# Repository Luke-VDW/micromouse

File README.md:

# micromouse
This repository contains all documentation used and deliverables produced for the UCT EEE3088F micromouse project.

A micromouse is a battery powered robot whose goal is to navigate through a maze. The project focuses on the design of the micro-mouse’s hardware. The project is compartmentalised into four subsystems, namely: the motherboard, the processor, power and sensing. The processor subsystem and motherboard subsystem have been completed. This repository will contain the power subsystem and sensing subsystem documentation.

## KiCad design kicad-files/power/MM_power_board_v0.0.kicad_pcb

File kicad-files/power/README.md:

This folder contains all kicad material for the power subsystem of the micromouse project.

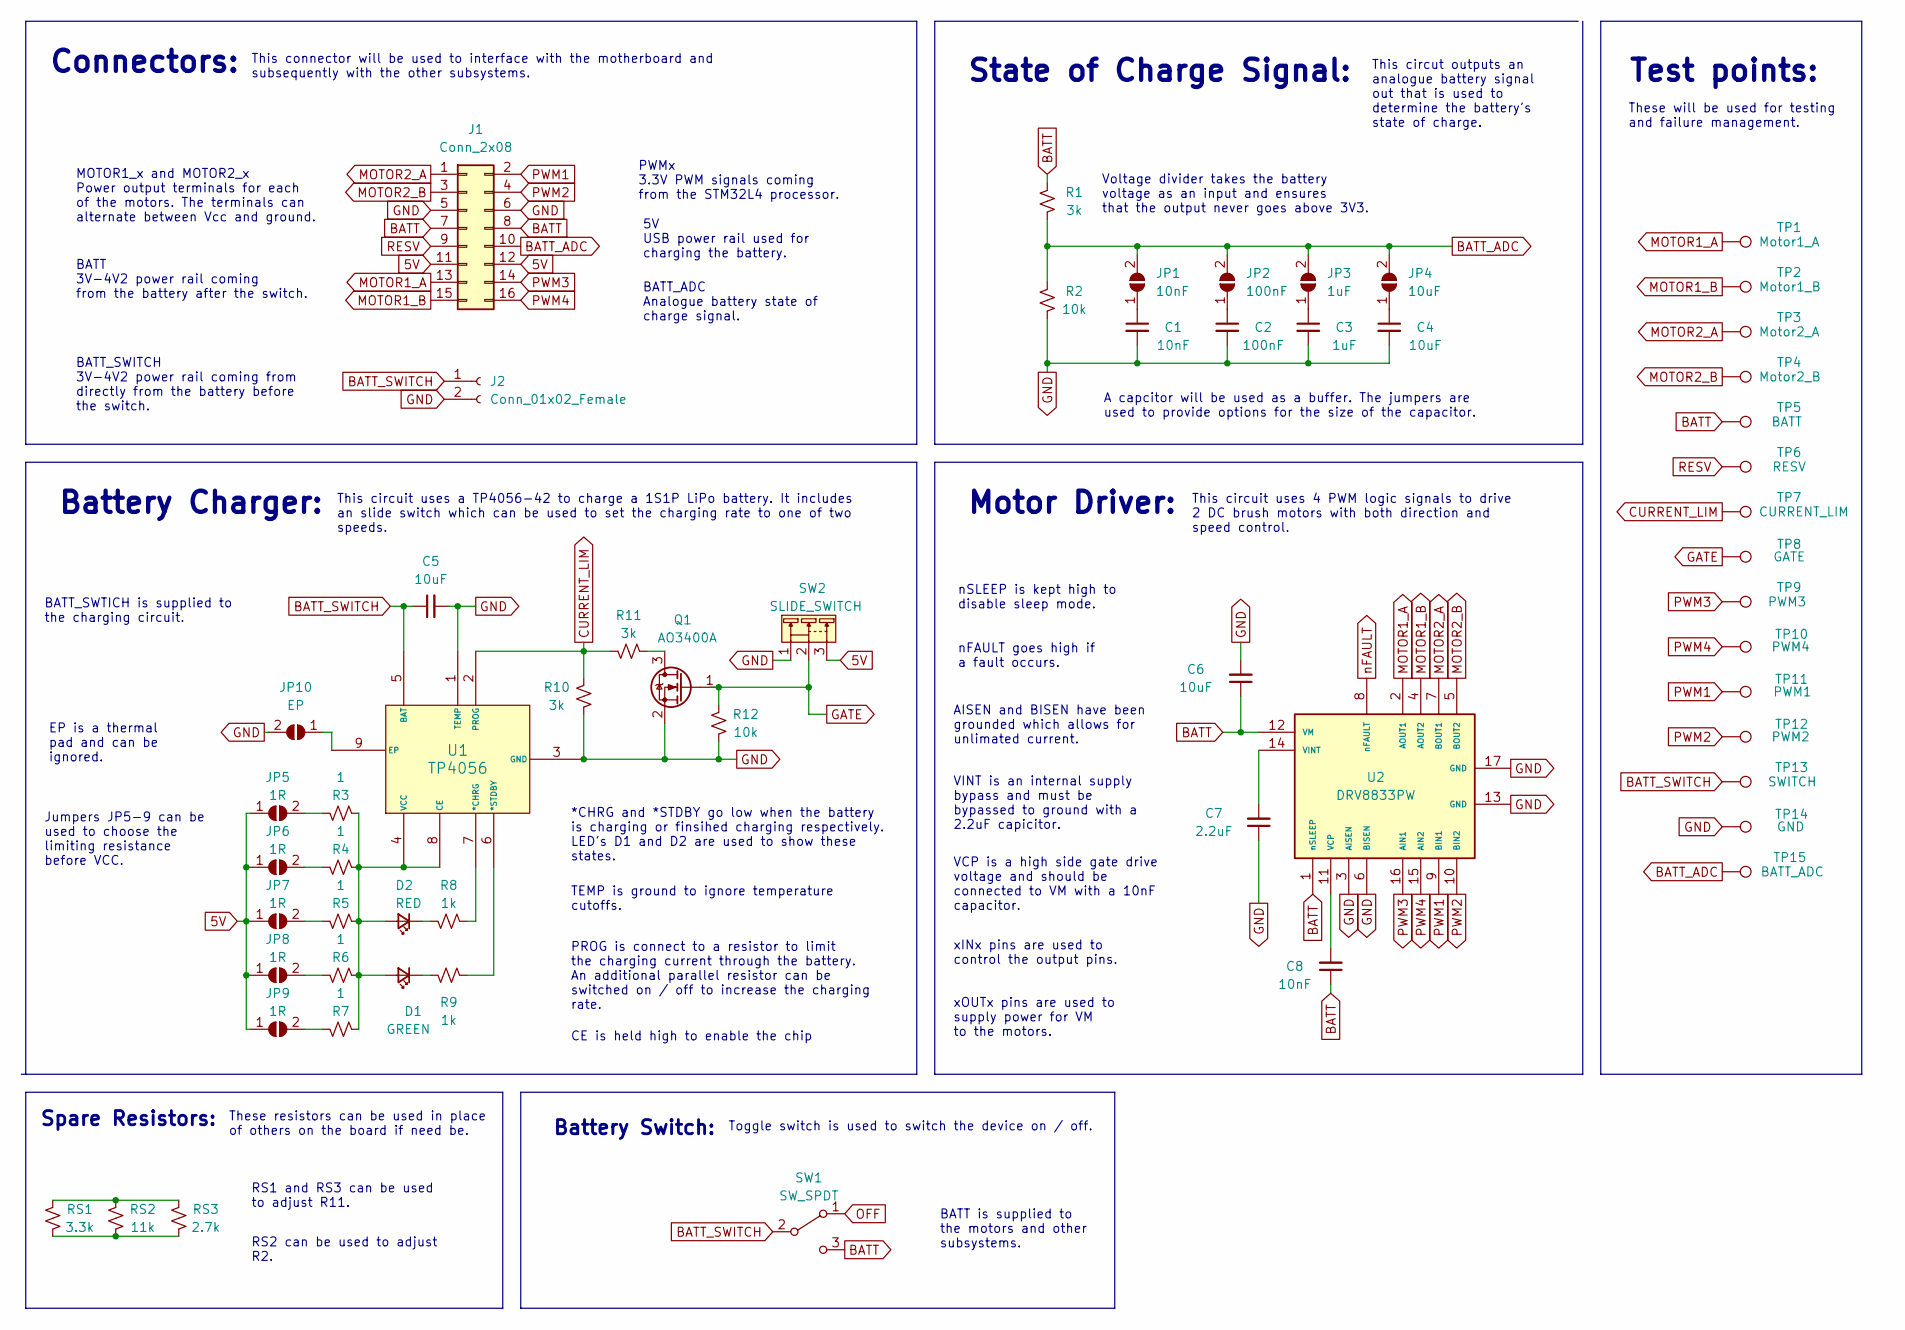
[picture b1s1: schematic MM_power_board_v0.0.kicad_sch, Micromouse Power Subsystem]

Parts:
C1, C8: 10nF; C_0603_1608Metric
C2: 100nF; C_0603_1608Metric
C3: 1uF; C_0603_1608Metric
C4, C5, C6: 10uF; C_0603_1608Metric
C7: 2.2uF; C_0603_1608Metric
D1: GREEN; LED0805-R-RD
D2: RED; LED0603-RD
J1: Conn_2x08; PinHeader_2x08_P2.54mm_Vertical
J2: Conn_01x02_Female; JST_PH_S2B-PH-K_1x02_P2.00mm_Horizontal
JP1: 10nF; SolderJumper-2_P1.3mm_Open_RoundedPad1.0x1.5mm
JP2: 100nF; SolderJumper-2_P1.3mm_Open_RoundedPad1.0x1.5mm
JP3: 1uF; SolderJumper-2_P1.3mm_Open_RoundedPad1.0x1.5mm
JP4: 10uF; SolderJumper-2_P1.3mm_Open_RoundedPad1.0x1.5mm
JP5, JP6, JP7, JP8, JP9: 1R; SolderJumper-2_P1.3mm_Open_RoundedPad1.0x1.5mm
JP10: EP; SolderJumper-2_P1.3mm_Open_RoundedPad1.0x1.5mm
Q1: AO3400A; SOT-23
R1, R10, R11: 3k; R_0603_1608Metric
R2, R12: 10k; R_0603_1608Metric
R3, R4, R5, R6, R7: 1; R_1206_3216Metric
R8, R9: 1k; R_0603_1608Metric
RS1: 3.3k; R_0603_1608Metric
RS2: 11k; R_0603_1608Metric
RS3: 2.7k; R_0603_1608Metric
SW1: SW_SPDT; SW-TH_MT-0-103-A101-M200-RS
SW2: SLIDE_SWITCH; SW-TH_SS-12D10L5
TP1: Motor1_A; TestPoint_Keystone_5000-5004_Miniature
TP2: Motor1_B; TestPoint_Keystone_5000-5004_Miniature
TP3: Motor2_A; TestPoint_Keystone_5000-5004_Miniature
TP4: Motor2_B; TestPoint_Keystone_5000-5004_Miniature
TP5: BATT; TestPoint_Keystone_5000-5004_Miniature
TP6: RESV; TestPoint_Keystone_5000-5004_Miniature
TP7: CURRENT_LIM; TestPoint_Keystone_5000-5004_Miniature
TP8: GATE; TestPoint_Keystone_5000-5004_Miniature
TP9: PWM3; TestPoint_Keystone_5000-5004_Miniature
TP10: PWM4; TestPoint_Keystone_5000-5004_Miniature
TP11: PWM1; TestPoint_Keystone_5000-5004_Miniature
TP12: PWM2; TestPoint_Keystone_5000-5004_Miniature
TP13: SWITCH; TestPoint_Keystone_5000-5004_Miniature
TP14: GND; TestPoint_Keystone_5000-5004_Miniature
TP15: BATT_ADC; TestPoint_Keystone_5000-5004_Miniature
U1: TP4056; ESOP-8_L4.9-W3.9-P1.27-LS6.0-BL-EP
U2: DRV8833PW; TSSOP-16_L5.0-W4.4-P0.65-LS6.4-BL-EP

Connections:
5V: J1.11, J1.12, JP5.1 (A), JP6.1 (A), JP7.1 (A), JP8.1 (A), JP9.1 (A), SW2.3
BATT: C6.1, C8.1, J1.7, J1.8, R1.2, SW1.3 (C), TP5.1, U2.1 (nSLEEP), U2.12 (VM)
BATT_ADC: J1.10, JP1.2 (B), JP2.2 (B), JP3.2 (B), JP4.2 (B), R1.1, R2.2, TP15.1
BATT_SWITCH: C5.1, J2.1, SW1.2 (B), TP13.1, U1.5 (BAT)
CURRENT_LIM: R10.2, R11.1, TP7.1, U1.2 (PROG)
GATE: Q1.1 (G), R12.1, SW2.2, TP8.1
GND: C1.2, C2.2, C3.2, C4.2, C5.2, C6.2, C7.1, J1.5, J1.6, J2.2, JP10.2 (B), Q1.2 (S), R2.1, R10.1, R12.2, SW2.1, TP14.1, U1.1 (TEMP), U1.3 (GND), U2.3 (AISEN), U2.6 (BISEN), U2.13 (GND), U2.17 (GND)
Motor1_A: J1.13, TP1.1, U2.2 (AOUT1)
Motor1_B: J1.15, TP2.1, U2.4 (AOUT2)
Motor2_A: J1.1, TP3.1, U2.7 (BOUT1)
Motor2_B: J1.3, TP4.1, U2.5 (BOUT2)
unnamed: C1.1, JP1.1 (A)
unnamed: C2.1, JP2.1 (A)
unnamed: C3.1, JP3.1 (A)
unnamed: C4.1, JP4.1 (A)
unnamed: C7.2, U2.14 (VINT)
unnamed: C8.2, U2.11 (VCP)
unnamed: D1.1 (K), R9.2
unnamed: D1.2 (A), D2.2 (A), R3.2, R4.2, R5.2, R6.2, R7.2, U1.4 (VCC), U1.8 (CE)
unnamed: D2.1 (K), R8.2
unnamed: JP5.2 (B), R3.1
unnamed: JP6.2 (B), R4.1
unnamed: JP7.2 (B), R5.1
unnamed: JP8.2 (B), R6.1
unnamed: JP9.2 (B), R7.1
unnamed: JP10.1 (A), U1.9 (EP)
unnamed: Q1.3 (D), R11.2
unnamed: R8.1, U1.7 (*CHRG)
unnamed: R9.1, U1.6 (*STDBY)
unnamed: RS1.1, RS2.1, RS3.1
unnamed: RS1.2, RS2.2, RS3.2
OFF: SW1.1 (A)
PWM1: J1.2, TP11.1, U2.9 (BIN1)
PWM2: J1.4, TP12.1, U2.10 (BIN2)
PWM3: J1.14, TP9.1, U2.16 (AIN1)
PWM4: J1.16, TP10.1, U2.15 (AIN2)
RESV: J1.9, TP6.1
nFAULT: U2.8 (nFAULT)

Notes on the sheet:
BATT is supplied to the motors and other subsystems.
EP is a thermal pad and can be ignored.
Battery Charger:
Jumpers JP5-9 can be used to choose the limiting resistance before VCC.
Voltage divider takes the battery voltage as an input and ensures that the output never goes above 3V3.
A capcitor will be used as a buffer. The jumpers are used to provide options for the size of the capacitor.
VINT is an internal supply bypass and must be bypassed to ground with a 2.2uF capicitor.
This circuit uses 4 PWM logic signals to drive 2 DC brush motors with both direction and speed control.
These resistors can be used in place of others on the board if need be.
BATT_ADC Analogue battery state of charge signal.
nFAULT goes high if a fault occurs.
State of Charge Signal:
These will be used for testing and failure management.
BATT 3V-4V2 power rail coming from the battery after the switch.
This circut outputs an analogue battery signal out that is used to determine the battery's state of charge.
RS2 can be used to adjust R2.
PROG is connect to a resistor to limit the charging current through the battery. An additional parallel resistor can be switched on / off to increase the charging rate.
BATT_SWITCH 3V-4V2 power rail coming from directly from the battery before the switch.
CE is held high to enable the chip
VCP is a high side gate drive voltage and should be connected to VM with a 10nF capacitor.
Connectors:
Battery Switch:
This connector will be used to interface with the motherboard and subsequently with the other subsystems.
xINx pins are used to control the output pins.
PWMx 3.3V PWM signals coming from the STM32L4 processor.
xOUTx pins are used to supply power for VM to the motors.
Spare Resistors:
TEMP is ground to ignore temperature cutoffs.
AISEN and BISEN have been grounded which allows for unlimated current.
RS1 and RS3 can be used to adjust R11.
5V USB power rail used for charging the battery.
Test points:
nSLEEP is kept high to disable sleep mode.
BATT_SWTICH is supplied to the charging circuit.
MOTOR1_x and MOTOR2_x Power output terminals for each of the motors. The terminals can alternate between Vcc and ground.
Toggle switch is used to switch the device on / off.
Motor Driver:
*CHRG and *STDBY go low when the battery is charging or finsihed charging respectively. LED's D1 and D2 are used to show these states.
This circuit uses a TP4056-42 to charge a 1S1P LiPo battery. It includes an slide switch which can be used to set the charging rate to one of two speeds.

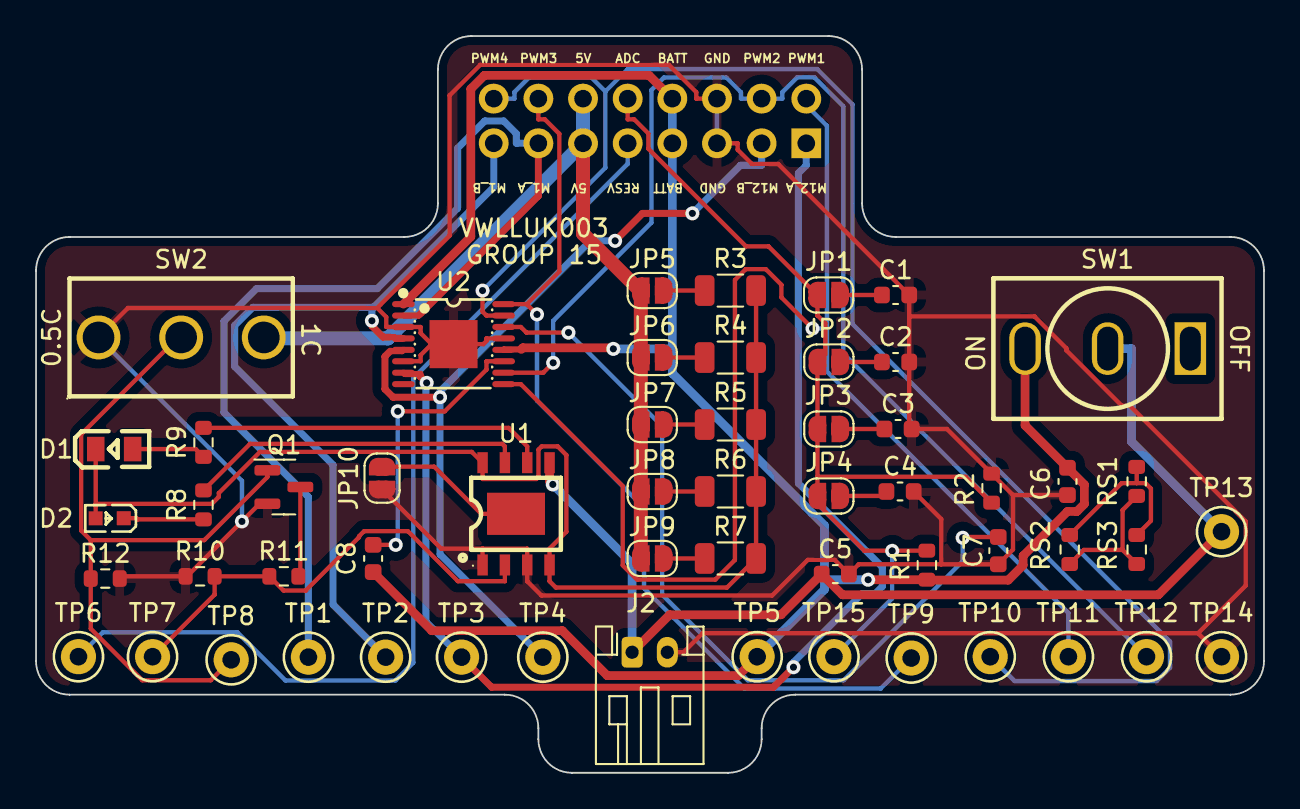
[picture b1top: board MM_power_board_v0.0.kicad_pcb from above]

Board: 2 copper layers, 69.9 x 41.9 mm, 57 parts (1 on the bottom side), 36 nets.

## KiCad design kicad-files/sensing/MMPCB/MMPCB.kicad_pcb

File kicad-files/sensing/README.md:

This folder contains all kicad material for the sensing subsystem of the micromouse project.

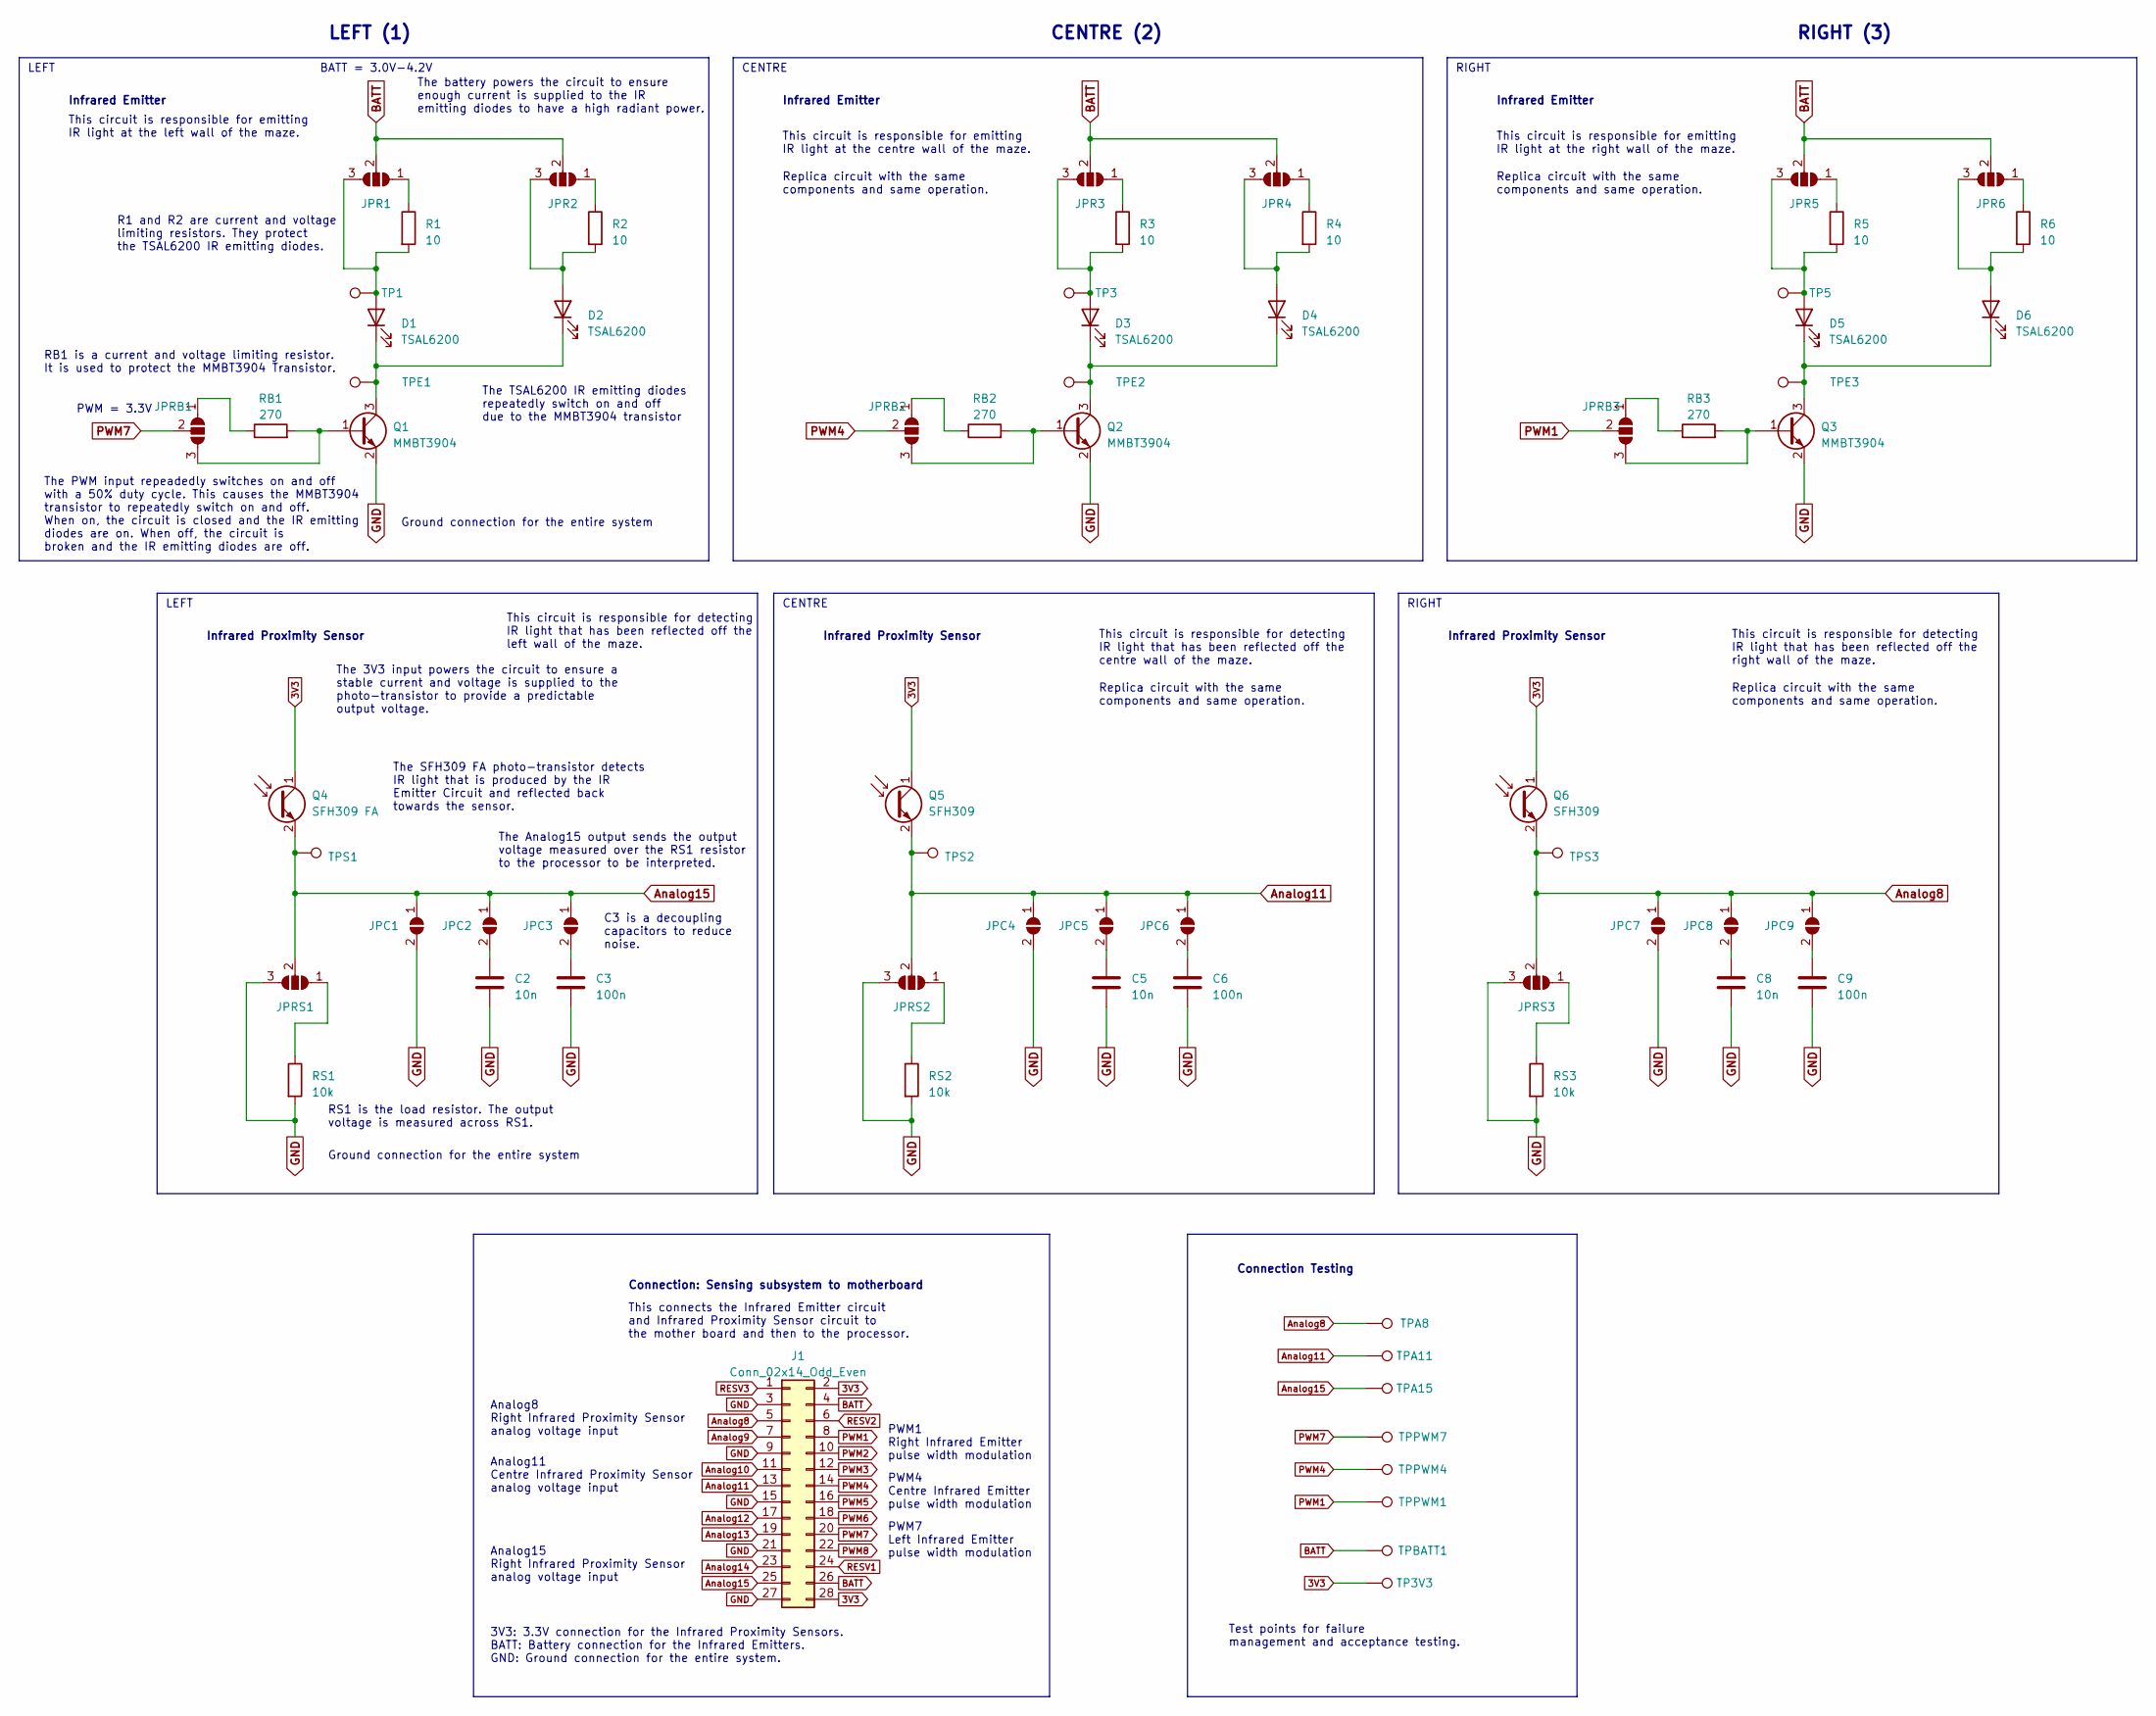
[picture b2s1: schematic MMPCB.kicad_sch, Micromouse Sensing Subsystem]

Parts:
C2, C5, C8: 10n; C_0603_1608Metric
C3, C6, C9: 100n; C_0603_1608Metric
D1, D2, D3, D4, D5, D6: TSAL6200; LED_D5.0mm_Horizontal_O1.27mm_Z3.0mm_Clear
J1: Conn_02x14_Odd_Even; PinHeader_2x14_P2.54mm_Vertical
JPC1, JPC2, JPC3, JPC4, JPC5, JPC6, JPC7, JPC8, JPC9: SolderJumper-2_P1.3mm_Open_RoundedPad1.0x1.5mm
JPR1, JPR2, JPR3, JPR4, JPR5, JPR6: SolderJumper-3_P1.3mm_Open_RoundedPad1.0x1.5mm_NumberLabels
JPRB1, JPRB2, JPRB3: SolderJumper-3_P1.3mm_Open_RoundedPad1.0x1.5mm_NumberLabels
JPRS1, JPRS2, JPRS3: SolderJumper-3_P1.3mm_Open_RoundedPad1.0x1.5mm_NumberLabels
Q1, Q2, Q3: MMBT3904; SOT-23
Q4: SFH309 FA; LED_D3.0mm_Horizontal_O1.27mm_Z2.0mm_Clear
Q5, Q6: SFH309; LED_D3.0mm_Horizontal_O1.27mm_Z2.0mm_Clear
R1, R2, R3, R4, R5, R6: 10; R_0603_1608Metric
RB1, RB2, RB3: 270; R_0603_1608Metric
RS1, RS2, RS3: 10k; R_0603_1608Metric
TP1, TP3, TP3V3, TP5: TestPoint_Pad_D1.5mm
TPA8, TPA11, TPA15: TestPoint_Pad_D1.5mm
TPBATT1: TestPoint_Pad_D1.5mm
TPE1, TPE2, TPE3: TestPoint_Pad_D1.5mm
TPPWM1, TPPWM4, TPPWM7: TestPoint_Pad_D1.5mm
TPS1, TPS2, TPS3: TestPoint_Pad_D1.5mm

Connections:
3V3: J1.2, J1.28, Q4.1 (C), Q5.1 (C), Q6.1 (C), TP3V3.1
Analog8: J1.5, JPC7.1 (A), JPC8.1 (A), JPC9.1 (A), JPRS3.2 (C), Q6.2 (E), TPA8.1, TPS3.1
Analog9: J1.7
Analog10: J1.11
Analog11: J1.13, JPC4.1 (A), JPC5.1 (A), JPC6.1 (A), JPRS2.2 (C), Q5.2 (E), TPA11.1, TPS2.1
Analog12: J1.17
Analog13: J1.19
Analog14: J1.23
Analog15: J1.25, JPC1.1 (A), JPC2.1 (A), JPC3.1 (A), JPRS1.2 (C), Q4.2 (E), TPA15.1, TPS1.1
BATT: J1.4, J1.26, JPR1.2 (C), JPR2.2 (C), JPR3.2 (C), JPR4.2 (C), JPR5.2 (C), JPR6.2 (C), TPBATT1.1
GND: C2.2, C3.2, C5.2, C6.2, C8.2, C9.2, J1.3, J1.9, J1.15, J1.21, J1.27, JPC1.2 (B), JPC4.2 (B), JPC7.2 (B), JPRS1.3 (B), JPRS2.3 (B), JPRS3.3 (B), Q1.2 (E), Q2.2 (E), Q3.2 (E), RS1.2, RS2.2, RS3.2
unnamed: D1.2 (A), JPR1.3 (B), R1.2, TP1.1
unnamed: D1.1 (K), D2.1 (K), Q1.3 (C), TPE1.1
unnamed: D2.2 (A), JPR2.3 (B), R2.2
unnamed: D3.2 (A), JPR3.3 (B), R3.2, TP3.1
unnamed: D3.1 (K), D4.1 (K), Q2.3 (C), TPE2.1
unnamed: D4.2 (A), JPR4.3 (B), R4.2
unnamed: D5.2 (A), JPR5.3 (B), R5.2, TP5.1
unnamed: D5.1 (K), D6.1 (K), Q3.3 (C), TPE3.1
unnamed: D6.2 (A), JPR6.3 (B), R6.2
unnamed: C2.1, JPC2.2 (B)
unnamed: C3.1, JPC3.2 (B)
unnamed: C5.1, JPC5.2 (B)
unnamed: C6.1, JPC6.2 (B)
unnamed: C8.1, JPC8.2 (B)
unnamed: C9.1, JPC9.2 (B)
unnamed: JPR1.1 (A), R1.1
unnamed: JPR2.1 (A), R2.1
unnamed: JPR3.1 (A), R3.1
unnamed: JPR4.1 (A), R4.1
unnamed: JPR5.1 (A), R5.1
unnamed: JPR6.1 (A), R6.1
unnamed: JPRB1.1 (A), RB1.1
unnamed: JPRB1.3 (B), Q1.1 (B), RB1.2
unnamed: JPRB2.1 (A), RB2.1
unnamed: JPRB2.3 (B), Q2.1 (B), RB2.2
unnamed: JPRB3.1 (A), RB3.1
unnamed: JPRB3.3 (B), Q3.1 (B), RB3.2
unnamed: JPRS1.1 (A), RS1.1
unnamed: JPRS2.1 (A), RS2.1
unnamed: JPRS3.1 (A), RS3.1
PWM1: J1.8, JPRB3.2 (C), TPPWM1.1
PWM2: J1.10
PWM3: J1.12
PWM4: J1.14, JPRB2.2 (C), TPPWM4.1
PWM5: J1.16
PWM6: J1.18
PWM7: J1.20, JPRB1.2 (C), TPPWM7.1
PWM8: J1.22
RESV1: J1.24
RESV2: J1.6
RESV3: J1.1

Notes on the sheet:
Test points for failure management and acceptance testing.
This connects the Infrared Emitter circuit and Infrared Proximity Sensor circuit to the mother board and then to the processor.
RIGHT
The SFH309 FA photo-transistor detects IR light that is produced by the IR Emitter Circuit and reflected back towards the sensor.
Analog11 Centre Infrared Proximity Sensor analog voltage input
Replica circuit with the same components and same operation.
LEFT
Infrared Proximity Sensor
PWM7 Left Infrared Emitter pulse width modulation
The PWM input repeadedly switches on and off with a 50% duty cycle. This causes the MMBT3904 transistor to repeatedly switch on and off. When on, the circuit is closed and the IR emitting diodes are on. When off, the circuit is broken and the IR emitting diodes are off.
This circuit is responsible for detecting IR light that has been reflected off the left wall of the maze.
C3 is a decoupling capacitors to reduce noise.
Analog8 Right Infrared Proximity Sensor analog voltage input
This circuit is responsible for emitting IR light at the left wall of the maze.
This circuit is responsible for detecting IR light that has been reflected off the centre wall of the maze.
The 3V3 input powers the circuit to ensure a stable current and voltage is supplied to the photo-transistor to provide a predictable output voltage.
PWM1 Right Infrared Emitter pulse width modulation
PWM = 3.3V
Connection Testing
This circuit is responsible for emitting IR light at the centre wall of the maze.
The Analog15 output sends the output voltage measured over the RS1 resistor to the processor to be interpreted.
RS1 is the load resistor. The output voltage is measured across RS1.
LEFT (1)
Infrared Emitter
RIGHT (3)
This circuit is responsible for detecting IR light that has been reflected off the right wall of the maze.
BATT = 3.0V-4.2V
Ground connection for the entire system
PWM4 Centre Infrared Emitter pulse width modulation
Analog15 Right Infrared Proximity Sensor analog voltage input
CENTRE (2)
The TSAL6200 IR emitting diodes repeatedly switch on and off due to the MMBT3904 transistor
CENTRE
3V3: 3.3V connection for the Infrared Proximity Sensors. BATT: Battery connection for the Infrared Emitters. GND: Ground connection for the entire system.
R1 and R2 are current and voltage limiting resistors. They protect the TSAL6200 IR emitting diodes.
This circuit is responsible for emitting IR light at the right wall of the maze.
Connection: Sensing subsystem to motherboard
The battery powers the circuit to ensure enough current is supplied to the IR emitting diodes to have a high radiant power.
RB1 is a current and voltage limiting resistor. It is used to protect the MMBT3904 Transistor.

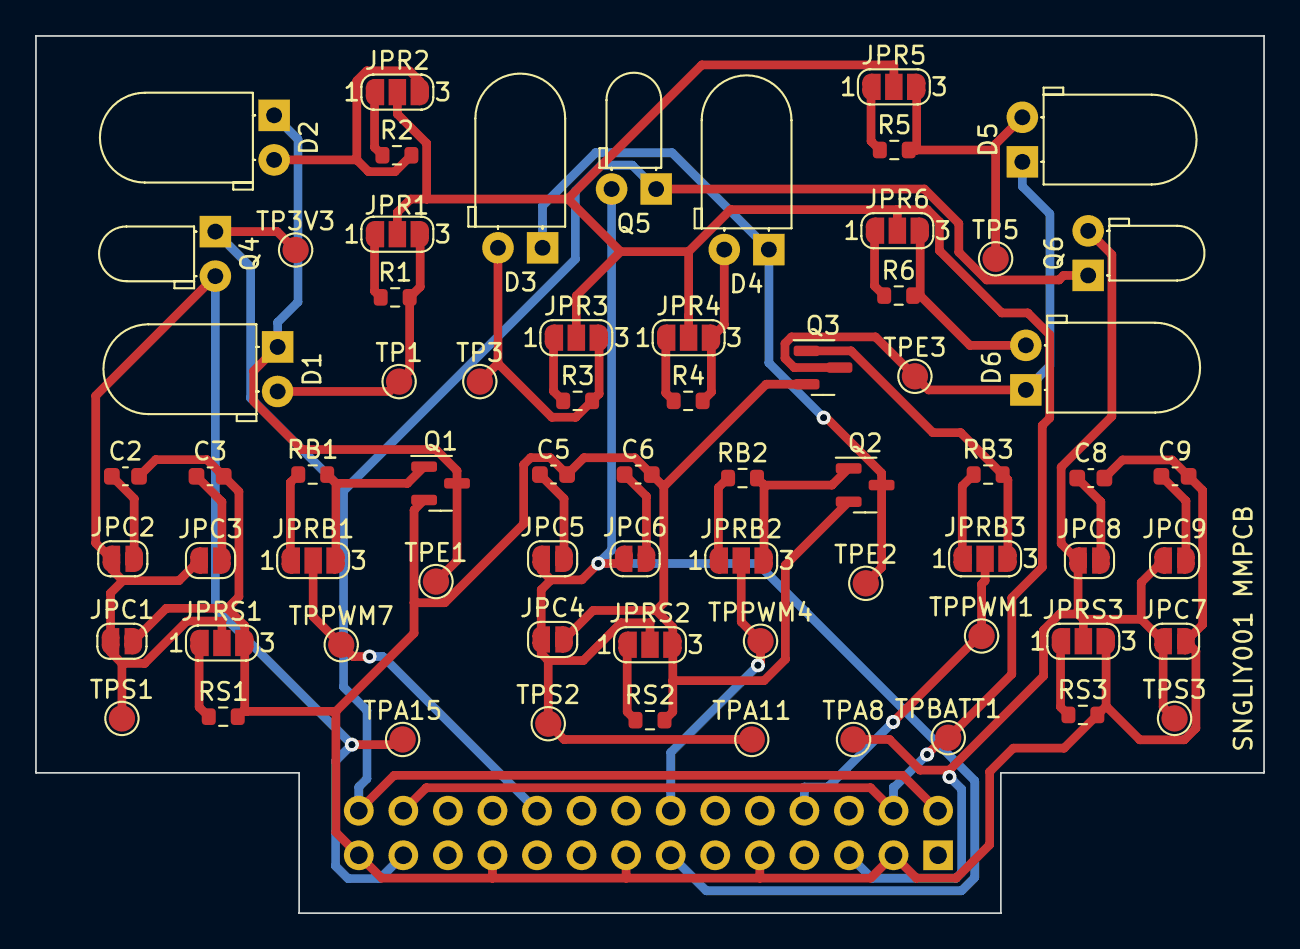
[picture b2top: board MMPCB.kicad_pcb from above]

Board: 2 copper layers, 70.0 x 50.0 mm, 69 parts (1 on the bottom side), 39 nets.

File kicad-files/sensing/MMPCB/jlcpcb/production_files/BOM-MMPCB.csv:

Comment,Designator,Footprint,LCSC
100n,"C3,C6,C9",C_0603_1608Metric,C14663
MMBT3904,"Q1,Q2,Q3",SOT-23,C20526
10,"R1,R2,R3,R4,R5,R6",R_0603_1608Metric,C22859
270,"RB1,RB2,RB3",R_0603_1608Metric,C22966
10k,"RS1,RS2,RS3",R_0603_1608Metric,C25804
SFH309,"Q4,Q5,Q6",LED_D3.0mm_Horizontal_O1.27mm_Z2.0mm_Clear,C2900253
LED,"D1,D2,D3,D4,D5,D6",LED_D5.0mm_Horizontal_O1.27mm_Z3.0mm_Clear,C55528
10n,"C2,C5,C8",C_0603_1608Metric,C57112

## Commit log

2024-03-14 Create power_doc
2024-03-19 Update power_doc
2024-03-19 Create filler
2024-03-20 Added system-diagram.drawio
2024-03-20 Added system-diagram.drawio v0.0
2024-04-08 Add files via upload
    Update project description file.
2024-04-08 Delete documents/EEE3088F_2024_project_description_v5.pdf
    Removed old project description
2024-04-08 Added system-diagram.drawio.png
2024-04-19 Added power-module-section-diagram.drawio
2024-04-21 Added interfacing-diagram.drawio
2024-04-21 Create datasheets
2024-04-21 Create hi
